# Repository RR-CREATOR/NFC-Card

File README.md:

# RRcard

RRcard is my NFC business card / hacker card. It uses an NT3H2111 NFC chip with a PCB antenna, so tapping it with a phone can open my links without needing a QR code or typing anything manually.

I made this because normal business cards are kinda boring, and I wanted something that felt more like a PCB project than paper with text on it. I also wanted an excuse to KiCad, fight NFC antenna math, and see if I could get a tiny board fab-ready.

## Pictures

### Full 3D model

### PCB

### Schematic

## PCB design files

The KiCad files are in [`PCB design files`](PCB%20design%20files).

The JLCPCB production files are in [`PCB design files/jlcpcb/production_files`](PCB%20design%20files/jlcpcb/production_files).

## JLCPCB order cost

The final JLCPCB cart total came out to **$21.78 USD**.

## BOM

| Comment | Designator | Footprint | LCSC Part # | Quantity |
| --- | --- | --- | --- | ---: |
| 805 | LED1 | C2296_LED0805-R-RD | C84256 | 1 |
| 220nF | C1 | C_0603_1608Metric | C21120 | 1 |
| 47 | R1 | R_0603_1608Metric | C23182 | 1 |
| NT3H2111W0FHKH | U1 | C710403_XQFN-8_L1_6-W1_6-P0_50-BL_NT3H2111W0FHKH | C710403 | 1 |

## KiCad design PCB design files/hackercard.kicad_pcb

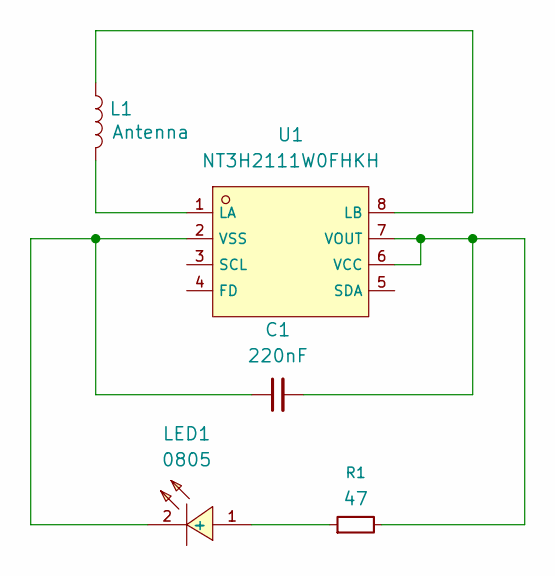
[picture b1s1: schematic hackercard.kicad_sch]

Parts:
C1: 220nF; C_0603_1608Metric; JLC Part # C21120
L1: Antenna; antenna_coil
LED1: 0805; C2296_LED0805-R-RD; JLC Part # C84256
R1: 47; R_0603_1608Metric; JLC Part # C23182
U1: NT3H2111W0FHKH; C710403_XQFN-8_L1_6-W1_6-P0_50-BL_NT3H2111W0FHKH; JLC Part # C710403

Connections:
unnamed: LED1.1 (+), R1.1
unnamed: C1.1, LED1.2 (-), U1.2 (VSS)
unnamed: L1.2, U1.1 (LA)
unnamed: L1.1, U1.8 (LB)
unnamed: C1.2, R1.2, U1.6 (VCC), U1.7 (VOUT)

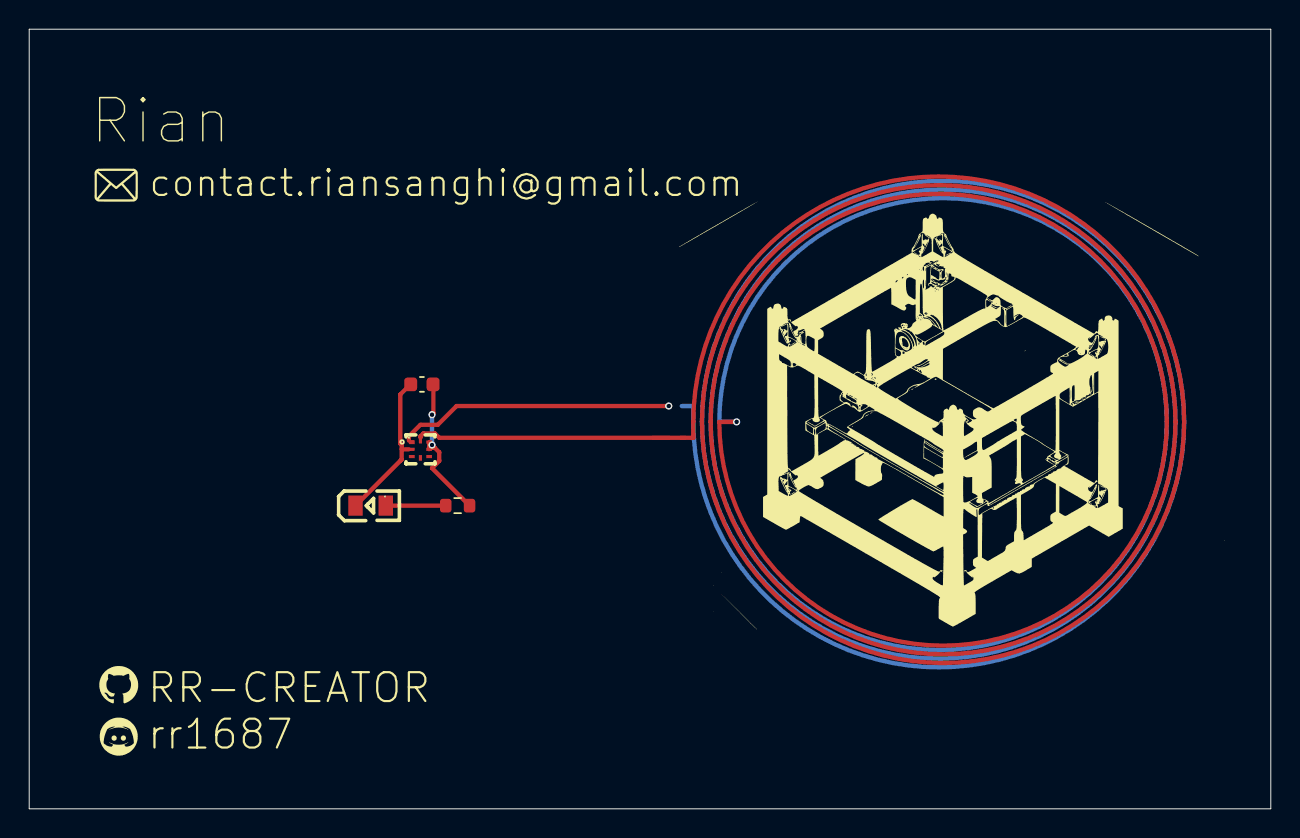
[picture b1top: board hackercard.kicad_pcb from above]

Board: 2 copper layers, 86.0 x 54.0 mm, 5 parts (0 on the bottom side), 5 nets.

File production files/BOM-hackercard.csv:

Comment,Designator,Footprint,LCSC,Quantity
805,LED1,C2296_LED0805-R-RD,C84256,1
220nF,C1,C_0603_1608Metric,C21120,1
47,R1,R_0603_1608Metric,C23182,1
NT3H2111W0FHKH,U1,C710403_XQFN-8_L1_6-W1_6-P0_50-BL_NT3H2111W0FHKH,C710403,1
